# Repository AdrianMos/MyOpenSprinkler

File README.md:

# myOpenSprinkler
open-source RaspberryPi sprinkler valve controller

This repo includes the KiCad project.

**Features:**
- designed for RaspberryPi Zero W
- small form factor

* inspired by OpenSprinkler Pi project
* supports OpenSprinkler software

- controls 8 zones (8x24VAC valves)
- optical insulation between the power-triacs and RaspberryPi 
- integrated 24VAC to 5V converter (no power connector required for RaspberryPi)
- includes a real-time-clock (RTC) module
- rain sensor input
- transient voltage protection

* connector for RFM12B radio transceiver (used for remote sensing/control)  [drivers not available yet]
* 1-wire communication for connecting external temperature sensors [drivers not available yet]

**Hardware v1.0:**

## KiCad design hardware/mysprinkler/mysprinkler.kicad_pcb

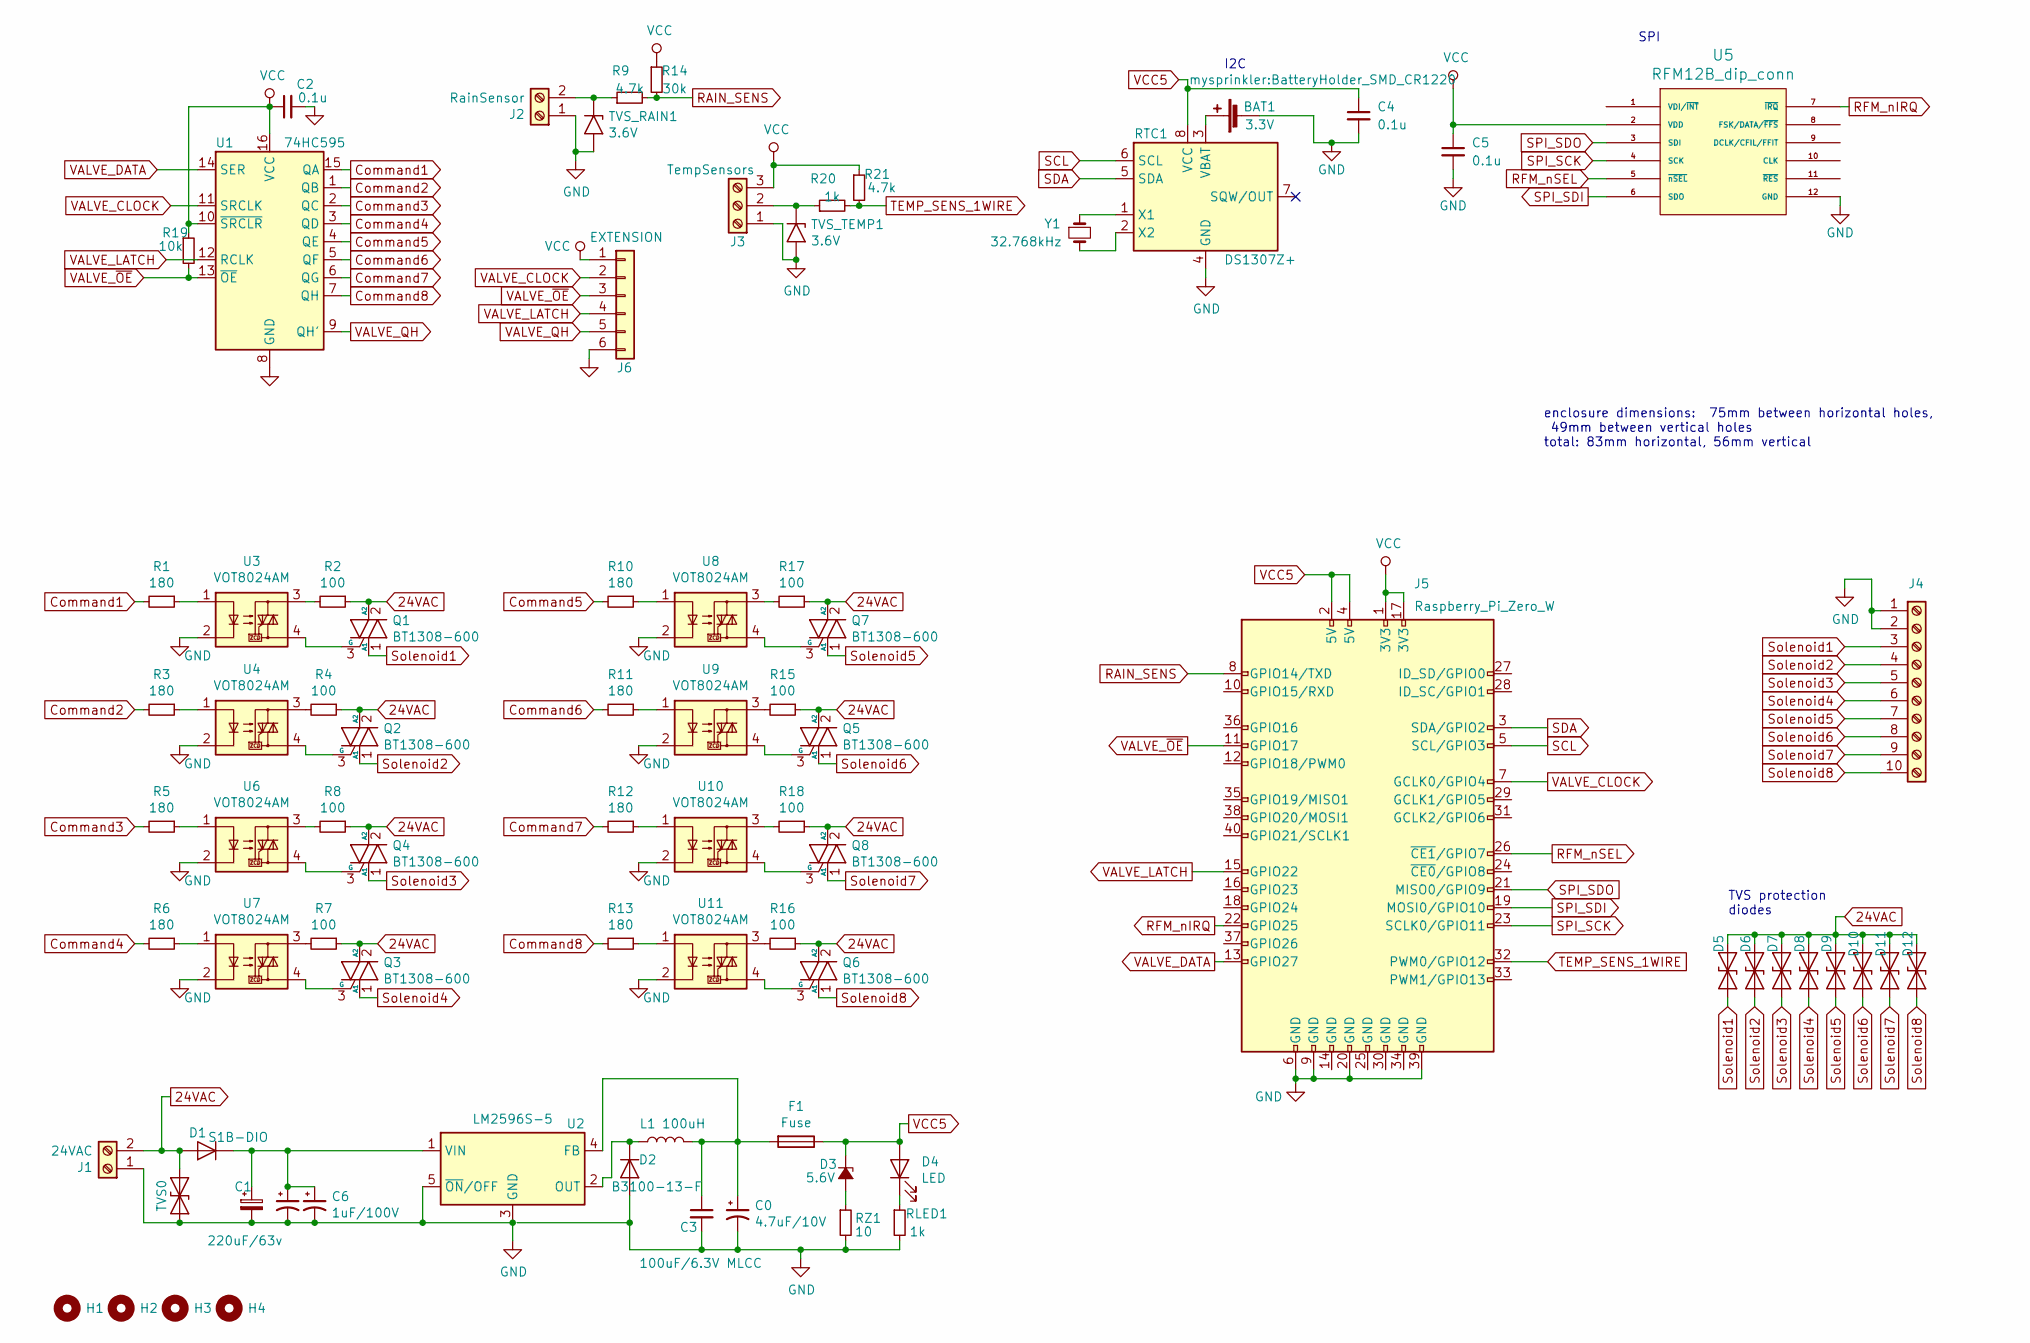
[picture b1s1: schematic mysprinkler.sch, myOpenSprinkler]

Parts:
BAT1: 3.3V; BatteryHolder_SMD_CR1220
C0: 4.7uF/10V; CP_EIA-3216-18_Kemet-A_Pad1.58x1.35mm_HandSolder
C1: 220uF/63v; C_Elec_10x10.2
C2, C4, C5: 0.1u; C_0805_2012Metric_Pad1.15x1.40mm_HandSolder
C3: 100uF/6.3V MLCC; CP_EIA-3528-21_Kemet-B_Pad1.50x2.35mm_HandSolder
C6: 1uF/100V; C_1206_3216Metric
C6b1: 2.2uF/100V; C_1206_3216Metric
D1: S1B-DIO; D_SMA
D2: B3100-13-F; D_SMC
D3: 5.6V; D_MiniMELF
D4: LED; LED_0805_2012Metric_Pad1.15x1.40mm_HandSolder
D5, D6, D7, D8, D9, D10, D11, D12: D_TVS; D_SMB
F1: Fuse; R_1812_4532Metric_Pad1.30x3.40mm_HandSolder
H1: MH1; MountingHole_6.4mm_M6
H2: 2; MountingHole_6.4mm_M6
H3: 3; MountingHole_6.4mm_M6
H4: 4; MountingHole_6.4mm_M6
J1: 24VAC; TerminalBlock_TE_282834-2_1x02_P2.54mm_Horizontal
J2: RainSensor; Molex_PicoBlade_53047-0210_1x02_P1.25mm_Vertical
J3: TempSensors; Molex_PicoBlade_53398-0371_1x03-1MP_P1.25mm_Vertical
J4: Screw_Terminal_01x10; TerminalBlock_TE_1-282834-0_1x10_P2.54mm_Horizontal
J5: Raspberry_Pi_Zero_W; RaspberryPi_connector_female
J6: EXTENSION; PinHeader_1x06_P2.54mm_Vertical
L1: 100uH; L_12x12mm_H8mm
Q1, Q2, Q3, Q4, Q5, Q6, Q7, Q8: BT1308-600; SOT-223-3_TabPin2
R1, R3, R5, R6, R10, R11, R12, R13: 180; R_1206_3216Metric_Pad1.42x1.75mm_HandSolder
R2, R4, R7, R8, R15, R16, R17, R18: 100; R_1206_3216Metric_Pad1.42x1.75mm_HandSolder
R9, R21: 4.7k; R_1206_3216Metric_Pad1.42x1.75mm_HandSolder
R14: 30k; R_1206_3216Metric_Pad1.42x1.75mm_HandSolder
R19: 10k; R_1206_3216Metric_Pad1.42x1.75mm_HandSolder
R20: 1k; R_1206_3216Metric_Pad1.42x1.75mm_HandSolder
RLED1: 1k; R_1206_3216Metric_Pad1.42x1.75mm_HandSolder
RTC1: DS1307Z+; SOIC-8_3.9x4.9mm_P1.27mm
RZ1: 10; R_1206_3216Metric_Pad1.42x1.75mm_HandSolder
TVS0: D_TVS; D_SMB
TVS_RAIN1: 3.6V; D_SMB
TVS_TEMP1: 3.6V; D_SMB
U1: 74HC595; SOIC-16_3.9x9.9mm_P1.27mm
U2: LM2596S-5; TO-263-5_TabPin3
U3, U4, U6, U7, U8, U9, U10, U11: VOT8024AM; SO-4_4.4x4.3mm_P2.54mm_handsolder
U5: RFM12B_dip_conn; PinSocket_2x06_P2.00mm_Vertical
Y1: 32.768kHz; Crystal_SMD_EuroQuartz_EQ161-2Pin_3.2x1.5mm_HandSoldering

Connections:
24VAC: D1.2 (A), D5.2 (A2), D6.2 (A2), D7.2 (A2), D8.2 (A2), D9.2 (A2), D10.2 (A2), D11.2 (A2), D12.2 (A2), J1.2, Q1.2 (A2), Q2.2 (A2), Q3.2 (A2), Q4.2 (A2), Q5.2 (A2), Q6.2 (A2), Q7.2 (A2), Q8.2 (A2), R2.1, R4.1, R7.1, R8.1, R15.1, R16.1, R17.1, R18.1, TVS0.2 (A2)
Command1: R1.2, U1.15 (QA)
Command2: R3.2, U1.1 (QB)
Command3: R5.2, U1.2 (QC)
Command4: R6.2, U1.3 (QD)
Command5: R10.2, U1.4 (QE)
Command6: R11.2, U1.5 (QF)
Command7: R12.2, U1.6 (QG)
Command8: R13.2, U1.7 (QH)
GND: BAT1.2 (-), C0.2, C1.2, C2.2, C3.2, C4.2, C5.2, C6.2, C6b1.2, D2.2 (A), J1.1, J2.1, J3.1, J4.1, J4.2, J5.6 (GND), J5.9 (GND), J5.20 (GND), J5.39 (GND), J6.6, RLED1.2, RTC1.4 (GND), RZ1.2, TVS0.1 (A1), TVS_RAIN1.2 (A2), TVS_TEMP1.2 (A2), U1.8 (GND), U2.3 (GND), U2.5 (~ON~/OFF), U3.2, U4.2, U5.12 (GND), U6.2, U7.2, U8.2, U9.2, U10.2, U11.2
unnamed: BAT1.1 (+), RTC1.3 (VBAT)
unnamed: C0.1, C3.1, F1.2, L1.2, U2.4 (FB)
unnamed: C1.1, C6.1, C6b1.1, D1.1 (K), U2.1 (VIN)
unnamed: D2.1 (K), L1.1, U2.2 (OUT)
unnamed: D3.2 (A), RZ1.1
unnamed: D4.1 (K), RLED1.1
unnamed: J2.2, R9.1, TVS_RAIN1.1 (A1)
unnamed: J3.2, R20.1, TVS_TEMP1.1 (A1)
unnamed: Q1.3 (G), U3.4
unnamed: Q2.3 (G), U4.4
unnamed: Q3.3 (G), U7.4
unnamed: Q4.3 (G), U6.4
unnamed: Q5.3 (G), U9.4
unnamed: Q6.3 (G), U11.4
unnamed: Q7.3 (G), U8.4
unnamed: Q8.3 (G), U10.4
unnamed: R1.1, U3.1
unnamed: R2.2, U3.3
unnamed: R3.1, U4.1
unnamed: R4.2, U4.3
unnamed: R5.1, U6.1
unnamed: R6.1, U7.1
unnamed: R7.2, U7.3
unnamed: R8.2, U6.3
unnamed: R10.1, U8.1
unnamed: R11.1, U9.1
unnamed: R12.1, U10.1
unnamed: R13.1, U11.1
unnamed: R15.2, U9.3
unnamed: R16.2, U11.3
unnamed: R17.2, U8.3
unnamed: R18.2, U10.3
unnamed: RTC1.1 (X1), Y1.1
unnamed: RTC1.2 (X2), Y1.2
RAIN_SENS: J5.8 (GPIO14/TXD), R9.2, R14.2
RFM_nIRQ: J5.22 (GPIO25), U5.7 (~IRQ)
RFM_nSEL: J5.26 (~CE1~/GPIO7), U5.5 (~nSEL)
SCL: J5.5 (SCL/GPIO3), RTC1.6 (SCL)
SDA: J5.3 (SDA/GPIO2), RTC1.5 (SDA)
SPI_SCK: J5.23 (SCLK0/GPIO11), U5.4 (SCK)
SPI_SDI: J5.19 (MOSI0/GPIO10), U5.6 (SDO)
SPI_SDO: J5.21 (MISO0/GPIO9), U5.3 (SDI)
Solenoid1: D5.1 (A1), J4.3, Q1.1 (A1)
Solenoid2: D6.1 (A1), J4.4, Q2.1 (A1)
Solenoid3: D7.1 (A1), J4.5, Q4.1 (A1)
Solenoid4: D8.1 (A1), J4.6, Q3.1 (A1)
Solenoid5: D9.1 (A1), J4.7, Q7.1 (A1)
Solenoid6: D10.1 (A1), J4.8, Q5.1 (A1)
Solenoid7: D11.1 (A1), J4.9, Q8.1 (A1)
Solenoid8: D12.1 (A1), J4.10, Q6.1 (A1)
TEMP_SENS_1WIRE: J5.32 (PWM0/GPIO12), R20.2, R21.2
VALVE_CLOCK: J5.7 (GCLK0/GPIO4), J6.2, U1.11 (SRCLK)
VALVE_DATA: J5.13 (GPIO27), U1.14 (SER)
VALVE_LATCH: J5.15 (GPIO22), J6.4, U1.12 (RCLK)
VALVE_QH: J6.5, U1.9 (QH')
VALVE_~OE: J5.11 (GPIO17), J6.3, R19.2, U1.13 (~OE)
VCC: C2.1, C5.1, J3.3, J5.1 (3V3), J5.17 (3V3), J6.1, R14.1, R19.1, R21.1, U1.10 (~SRCLR), U1.16 (VCC), U5.2 (VDD)
VCC5: C4.1, D3.1 (K), D4.2 (A), F1.1, J5.2 (5V), J5.4 (5V), RTC1.8 (VCC)

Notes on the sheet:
TVS protection diodes
I2C
SPI
enclosure dimensions: 75mm between horizontal holes, 49mm between vertical holes total: 83mm horizontal, 56mm vertical

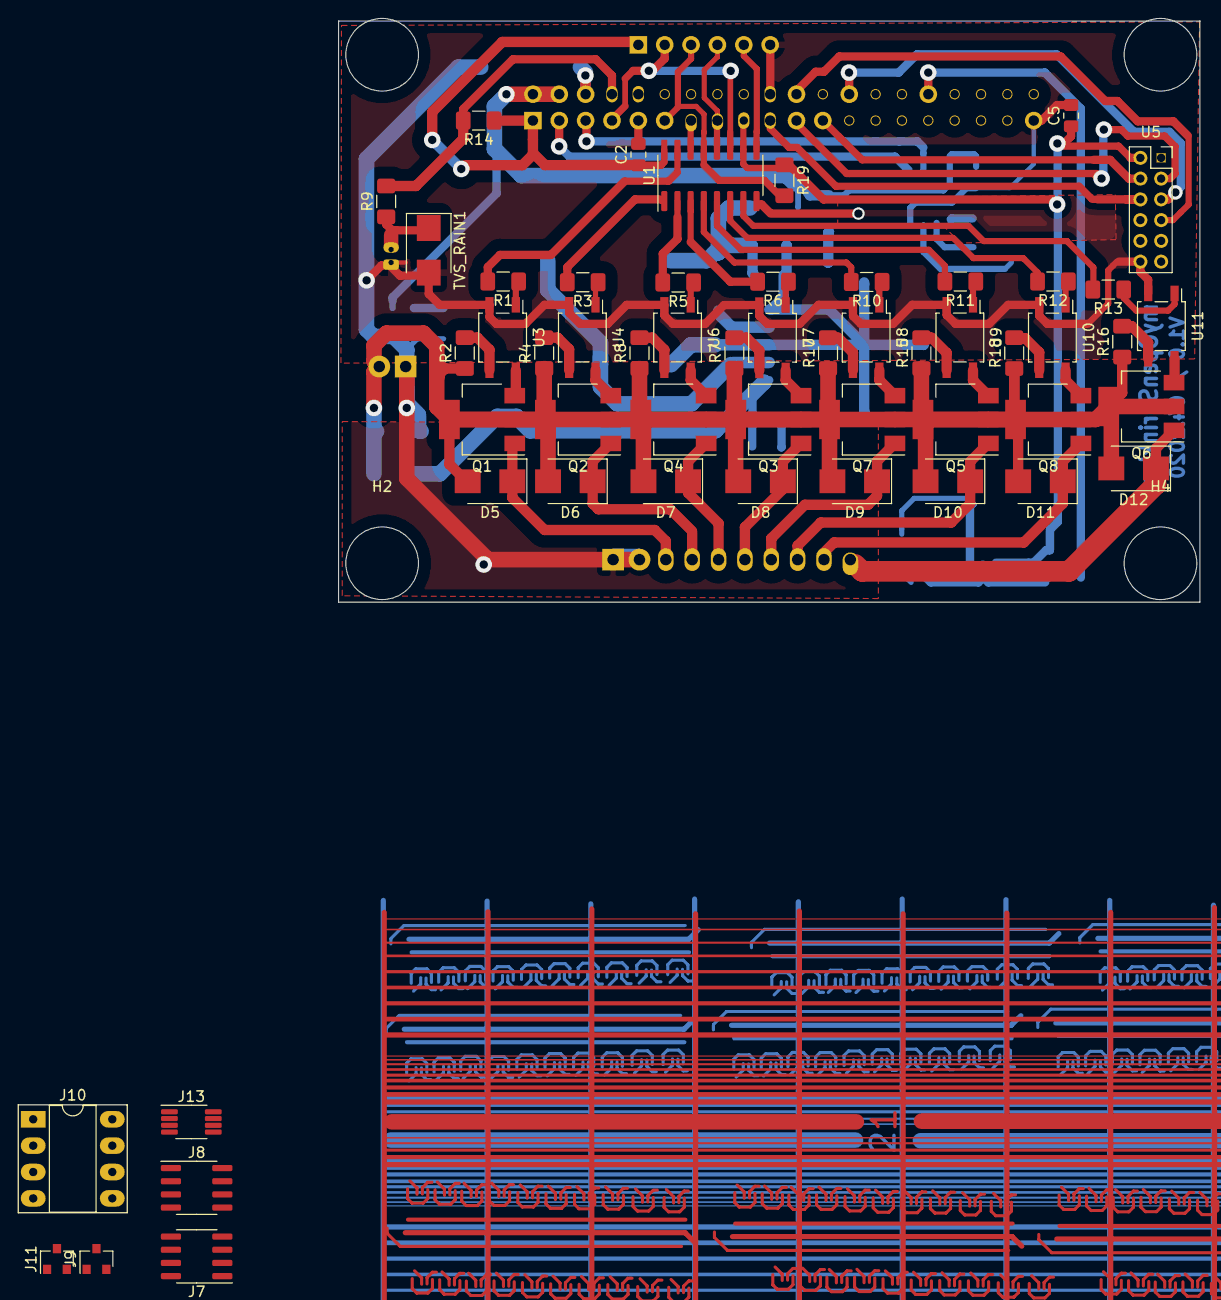
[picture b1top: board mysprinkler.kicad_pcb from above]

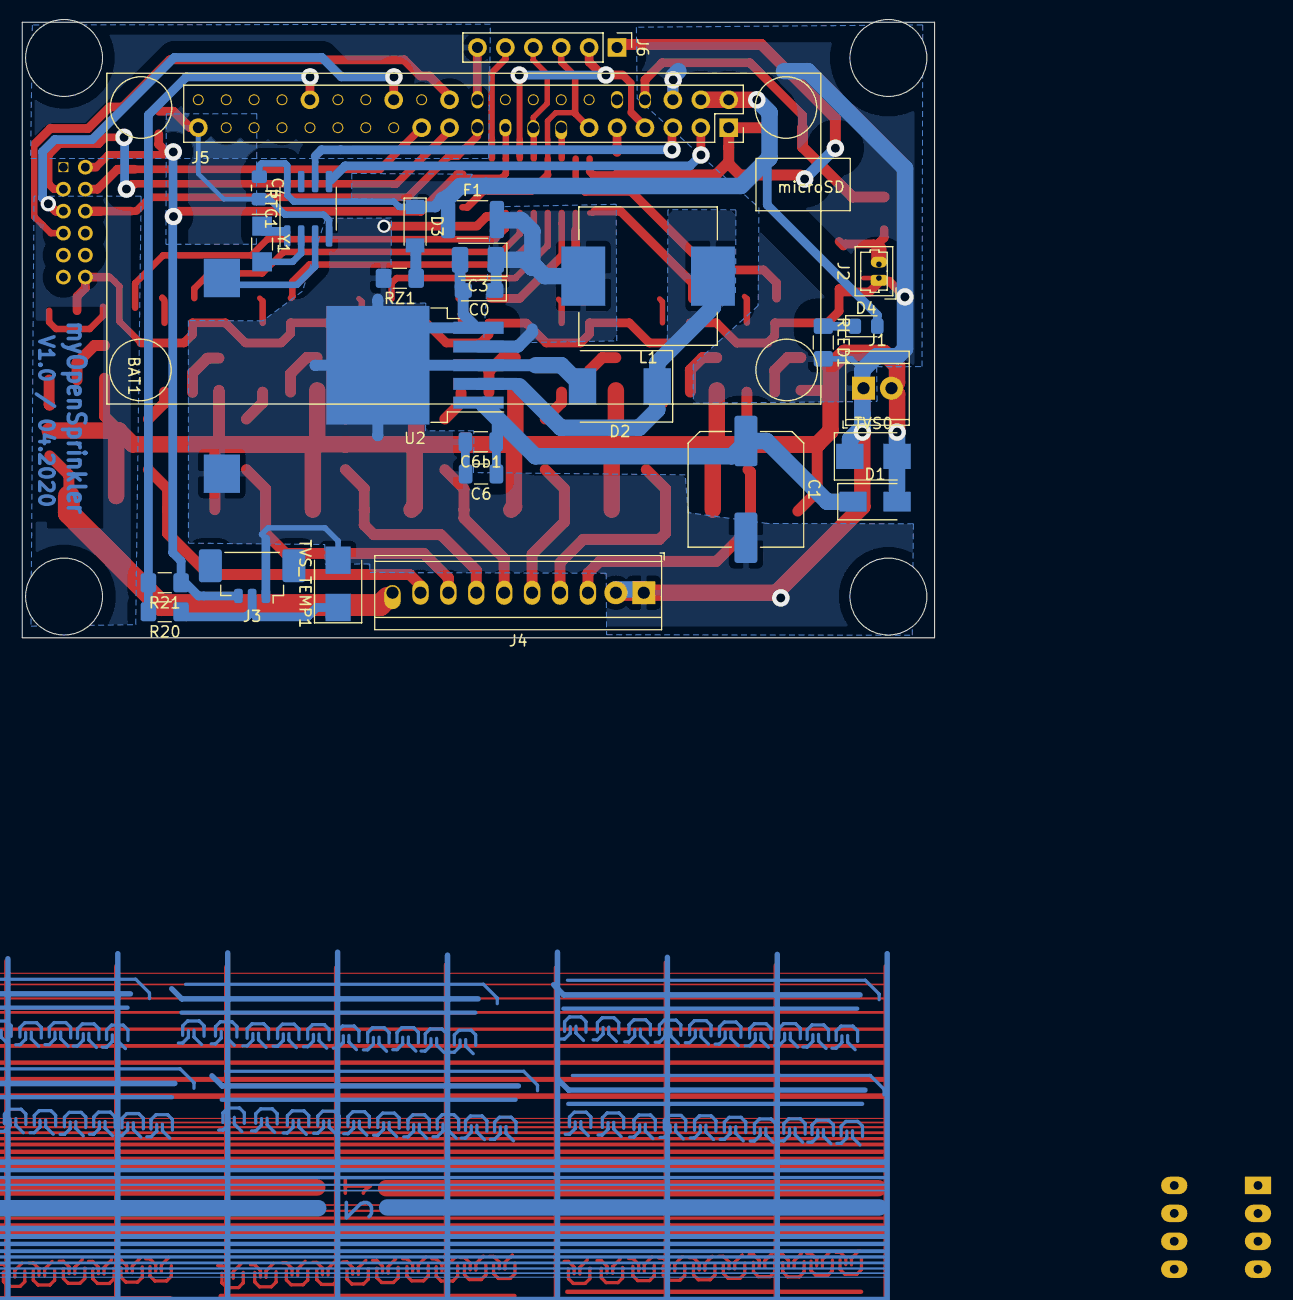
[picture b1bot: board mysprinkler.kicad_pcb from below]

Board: 2 copper layers, 83.0 x 56.0 mm, 86 parts (28 on the bottom side), 68 nets.

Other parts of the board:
J7, J8: SOIC8; SOIC-8_3.9x4.9mm_P1.27mm
J9, J11: SOT23; SOT-23
J10: DIP8; DIP-8_W7.62mm_Socket_LongPads
J13: MSOP8; MSOP-8_3x3mm_P0.65mm

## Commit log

2020-05-19 V1.0
2020-05-20 images for v1.0 board
2020-05-20 links to images in readme file
2020-05-23 case closed image

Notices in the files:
hardware/mysprinkler/mysprinkler.kicad_pcb:
License CC BY 4.0
hardware/mysprinkler/mysprinkler.sch:
https://creativecommons.org/licenses/by/4.0
